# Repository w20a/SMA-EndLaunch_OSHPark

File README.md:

# SMA-EndLaunch_OSHPark
Simulated and measured results of an end launch SMA landing pattern.

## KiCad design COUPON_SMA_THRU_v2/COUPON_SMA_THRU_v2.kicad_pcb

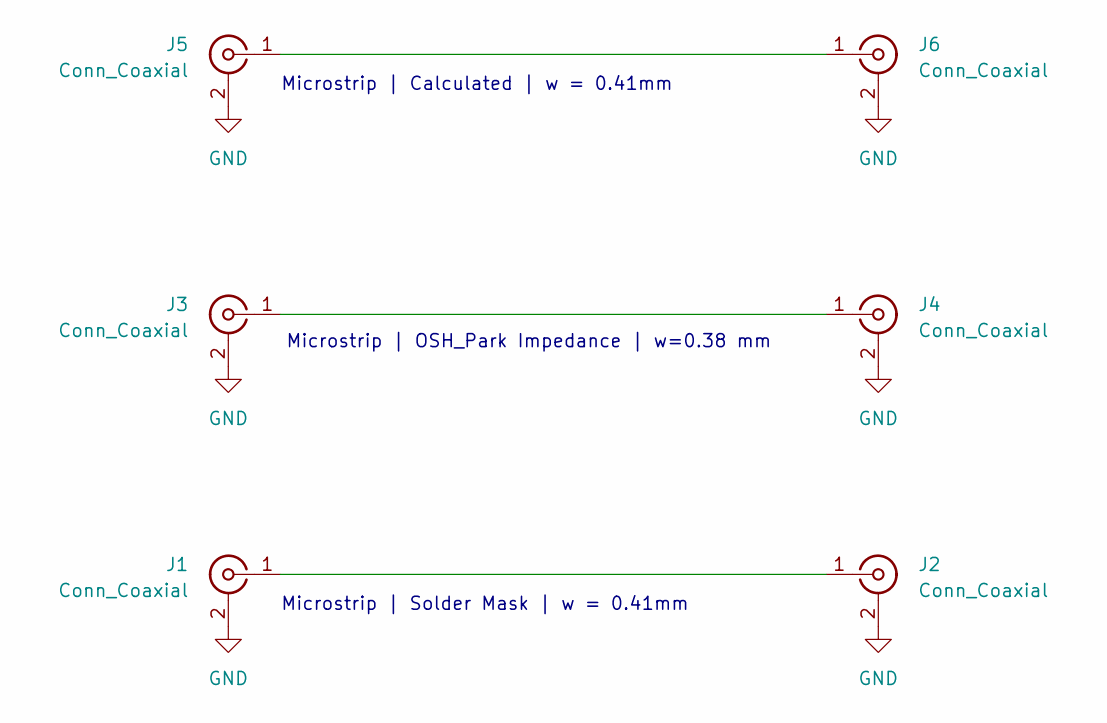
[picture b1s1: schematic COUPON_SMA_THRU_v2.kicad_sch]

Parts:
J1, J2, J3, J4, J5, J6: Conn_Coaxial; Conn_SMA

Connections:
GND: J1.2 (Ext), J2.2 (Ext), J3.2 (Ext), J4.2 (Ext), J5.2 (Ext), J6.2 (Ext)
unnamed: J1.1 (In), J2.1 (In)
unnamed: J3.1 (In), J4.1 (In)
unnamed: J5.1 (In), J6.1 (In)

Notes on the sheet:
Microstrip | OSH_Park Impedance | w=0.38 mm
Microstrip | Solder Mask | w = 0.41mm
Microstrip | Calculated | w = 0.41mm

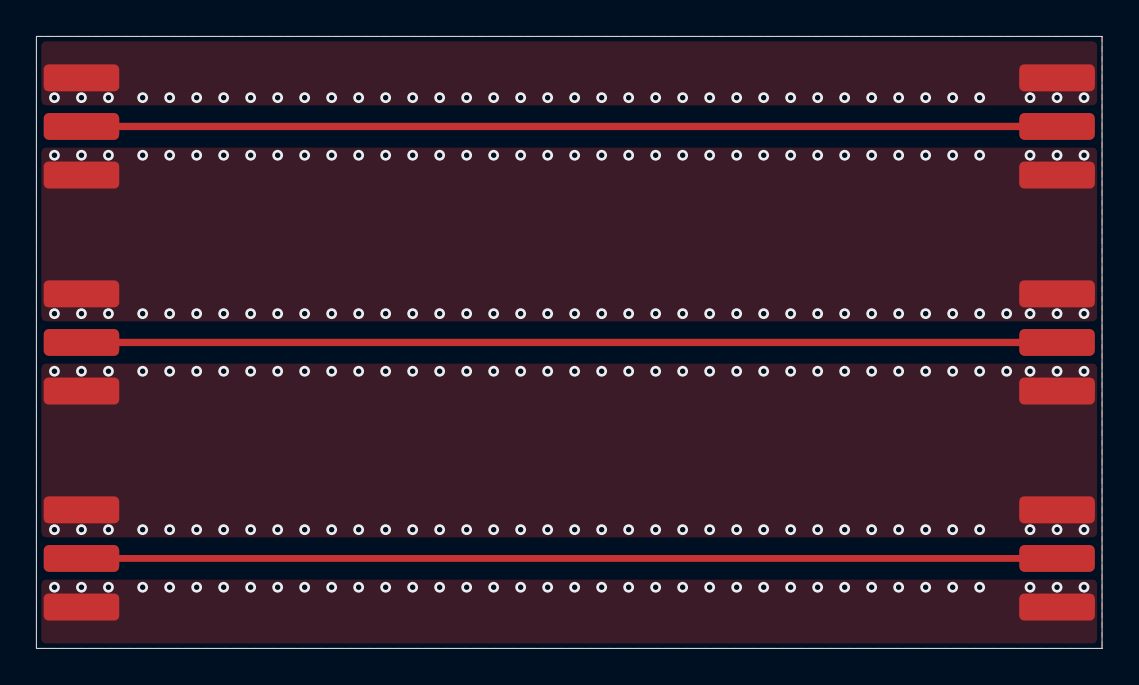
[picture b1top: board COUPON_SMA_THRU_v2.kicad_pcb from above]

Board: 4 copper layers, 59.2 x 34.0 mm, 6 parts (0 on the bottom side), 4 nets.

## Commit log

2026-06-07 Initial Data
    Initial results and simulated results obtained using CST
2026-06-07 Rename SMA_THRU_GCPW.s2p to GCPW_EM1_Simulated.s2p
2026-06-07 Rename SMA_THRU_Microstrip.s2p to EM1_Microstrip_Actual.s2p
2026-06-07 Rename EM1_Microstrip_Actual.s2p to Microstrip_EM1_Actual.s2p
2026-06-07 Rename uStrip_RFSOL_THRU.s1p to Microstrip_RFSol_Measured.s1p
2026-06-07 Rename GCPW_EM1_Simulated.s2p to GCPW_Samtec_Simulated.s2p
2026-06-07 Rename Microstrip_EM1_Actual.s2p to Microstrip_Samtec_Actual.s2p
2026-06-07 Rename Microstrip_Samtec_Actual.s2p to Microstrip_Samtec_Simulated.s2p
2026-06-07 Rename uStrip_SAMTEC_THRU.s1p to Microstrip_Samtec_Measured.s1p
2026-06-11 Upload original coupon
2026-06-11 Test
2026-06-11 Stackup edit
2026-06-12 Coupon SMA v2
